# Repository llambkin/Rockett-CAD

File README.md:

# Rockett CAD

Team Rockett!

Prepare for trouble!
And make it double!

To protect the world from devastation!
To unite all peoples within our nation!

To denounce the evils of truth and love!
To extend our reach to the stars above!

Liam
Mark

Team Rocket blasts off at the speed of light!
Surrender now, or prepare to fight!

Self-hosted, browser-based **parametric CAD** for designing 3D-printable parts.
This edition is single-user and opens without accounts or sign-in.
A deliberately simplified, self-hostable take on the parametric solid-modelling
portion of Fusion 360:

> **Sketch → constrain → feature → body → timeline → modify → regenerate → export**

Built on a real B-Rep solid-modelling kernel (OpenCascade / OCCT compiled to
WebAssembly), not a mesh editor. Every operation is an editable parametric
feature in a chronological timeline; editing an earlier feature rebuilds
everything downstream against persistent topology references.

## Features

### Sketch

- **Sketcher**: draw lines, rectangles, circles, arcs, polygons, slots, points and construction geometry.
- **Constraints and dimensions**: constrain shapes with editable dimensions; relation suggestions exclude duplicates and conflicting horizontal or vertical constraints.
- **Line angles**: a typed angle is kept; double-click a line to edit its length and angle.
- **Regions**: crossing and touching curves split a sketch into regions, such as the four corners around an inscribed circle.
- **Angle snap**: hold Shift to snap a line to 15 degree steps; press A to lock its angle.
- **Offsets**: offset a curve or chain; it follows its source as the sketch changes, and its distance stays editable.
- **Project, trim and extend**: link earlier model edges into a sketch, trim the highlighted piece of a curve (T), extend curves to boundaries.
- **Insert DXF and SVG**: place DXF or SVG drawings in a sketch, or SVG on a selected face, then size, rotate and position them.
- **Edit in place**: editing a sketch rolls the model back to it; Finish Sketch returns to the saved position.

### Model

- **Solid features**: extrude, revolve, sweep, loft, emboss and deboss from sketch profiles or planar faces.
- **Modify**: fillet, chamfer, shell, combine, split, press/pull and move bodies; shell with no open face hollows the body.
- **Tangent chains**: fillet and chamfer pick smooth connected edges in one click.
- **Replicate**: mirror, rectangular pattern and circular pattern.
- **Construction**: offset planes and midplanes; sketch on any planar face.
- **Reference images**: place PNG, JPEG or WebP images on planes and calibrate them to real size.
- **Feature timeline**: rename, edit, quick edit, hover preview, suppress, delete, roll back and insert features; broken references are flagged, never dropped.

### Inspect

- **Measure**: distance, ΔXYZ, angle, radius, area and length between points, edges and faces.

### Files

- **Import**: start or extend a project from a STEP, IGES, BREP, STL, OBJ or 3MF file. Meshes are not parametric.
- **Export**: download binary STL or multi-body 3MF with named bodies and a quality setting, or exact named solids as STEP.
- **Autosave**: every change saves to a readable JSON file that keeps the full feature history.
- **Edit conflicts**: reapply or discard conflicting edits; recovery clears stale undo history so it cannot overwrite another tab’s changes.

### Workspace

- **Viewport**: orbit, pan, zoom, named views and ViewCube; visible orthographic faces remain pickable, and graphics recovery redraws automatically.
- **Toolbar**: every tool shows an icon above its label; constraints show icons only; tooltips give the shortcut key.
- **Shortcuts**: single keys start tools; ? lists every keyboard and mouse control in a resizable panel that fills the window.
- **Undo and redo**: undo any edit, even inside a sketch, separately from the feature timeline.
- **Tool panels**: list stable pick labels; closing clears their highlight, and accepting an unchanged edit creates no undo step.
- **Groups**: gather selected bodies or sketches into named, collapsible tree folders with Ctrl+G or right-click.
- **Tree selection**: Ctrl or Cmd+click adds bodies or sketches, Shift+click selects a range; right-click acts on all.
- **Live preview**: feature dialogs keep the model before the feature pickable and ghost the result, green added, red removed, until OK.
- **Right-click menus**: project rows, tree items, timeline chips and the viewport offer their actions, sketch selections their relations; right-drag still orbits.
- **Projects**: sort into folders; create, rename, move or delete by button, right-click or drag; unreadable ones show why.
- **Project files**: download a project as one `.rockett` file, or open one as a new project.
- **This browser**: keep a project in this browser instead of on the server; move it either way by Move to or drag.
- **Reload**: refreshing the page reopens the project you had open; Back returns to the list.
- **Errors**: stay visible until dismissed, and their text can be copied.
- **Version label**: the bottom-right corner shows the running build; hover for commit, version and schema.

[docs/user/guide.md](docs/user/guide.md) explains how to use each one.

## Quick start (Docker)

```bash
ROCKETT_ALLOWED_ORIGINS=http://localhost:8788 docker compose up -d
```

Then open http://localhost:8788. The server refuses to start without
`ROCKETT_ALLOWED_ORIGINS`, the comma-separated browser origins allowed to
change projects; list the origin you browse to. All state lives in the
`rockett-cad_data` volume; DOCKER.md covers LAN access, running dev and prod
side by side, and promoting the image dev verified to prod.
The container runs as the unprivileged `rockett` user: `/app` is root-owned
and `/data` is the only path it writes.

For Unraid, see [DOCKER.md](DOCKER.md) and the template in
`docker/unraid-rockett-cad.xml`.

## Running build

The bottom-right corner of the project list and the workspace shows the
running build: the image's `git describe` output, else `v<version> <commit>`,
else `v<version> dev`. Hover it for the full commit, version and schema.
`GET /api/health` returns the same fields.

A plain `docker compose up` records neither, so the label reads
`v<version> dev`. For a granular label, build with
`--build-arg ROCKETT_COMMIT=$(git rev-parse HEAD) --build-arg ROCKETT_DESCRIBE=$(git describe --tags --always --dirty)`.
[DOCKER.md](DOCKER.md) has the full Compose and `docker build` commands.

## Development

```bash
npm ci                 # .npmrc: install scripts off, exact pins on save
npm run prepare        # once per clone: husky sets core.hooksPath to .husky/_
export ROCKETT_ALLOWED_ORIGINS=http://localhost:5173
npm run dev            # server on :8788 + Vite client on :5173
npm test               # typecheck, then shared, server and client tests
npm run lint           # oxlint
npm run format:check   # Prettier
npm run lint:readme    # README feature items stay within 20 words
npm run lint:comments  # comment ratchet: no file may gain a comment
npm run lint:writing   # writing lint over tracked markdown
```

The last two need masterrulez cloned to `~/masterrulez`. See
[DEVELOPMENT.md](DEVELOPMENT.md).

## Documentation

| Doc                                        | Contents                                                          |
| ------------------------------------------ | ----------------------------------------------------------------- |
| [docs/user/guide.md](docs/user/guide.md)   | How to use each feature, controls and shortcuts                   |
| [ARCHITECTURE.md](ARCHITECTURE.md)         | System overview, layers, technology choices                       |
| [CAD_MODEL.md](CAD_MODEL.md)               | B-Rep representation, topology naming, regeneration, tessellation |
| [FEATURE_TIMELINE.md](FEATURE_TIMELINE.md) | Timeline semantics, rollback, dependency handling                 |
| [API.md](API.md)                           | REST API reference                                                |
| [DOCKER.md](DOCKER.md)                     | Deployment (Docker / Compose / Unraid)                            |
| [DEVELOPMENT.md](DEVELOPMENT.md)           | Repo layout, workflows, testing                                   |
| [WORK-ORDER.md](WORK-ORDER.md)             | Scope, rulings and planned work                                   |
| [CHANGELOG.md](CHANGELOG.md)               | Changes per release, release and schema conventions               |
| [Brief.md](Brief.md)                       | Original 3D-printing brief, kept as history                       |

## License note

Rockett CAD bundles [opencascade.js](https://github.com/donalffons/opencascade.js)
(LGPL-2.1-only), the WASM build of Open CASCADE Technology.
[THIRD-PARTY-NOTICES.md](THIRD-PARTY-NOTICES.md) lists every third-party
package in the image and the client bundle, with its version, licence and the
obligations to meet before distribution.

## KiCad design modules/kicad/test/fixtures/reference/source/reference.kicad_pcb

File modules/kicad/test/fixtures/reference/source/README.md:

# Reference source

Hand-written KiCad 9 board and inline fixture footprints. No KiCad library
footprints or models are copied. Licence: UNLICENSED, pending the project's
licence decision. This preparation adds no redistribution grant.

The two STEP models came from Rockett's named STEP exporter. Each is a
scalene triangular prism, in mm. Only trailing line whitespace was removed
from the STEP exports:

| Model           | XY vertices         | Height | Volume |
| --------------- | ------------------- | ------ | ------ |
| fixture-wedge-a | (0,0), (8,0), (1,3) | 2      | 24 mm³ |
| fixture-wedge-b | (0,0), (5,0), (0,2) | 4      | 20 mm³ |

Grammar, layers and model fields follow the
[KiCad 9 writer](https://github.com/KiCad/kicad-source-mirror/blob/286b0611feca00727bf70bfa184ec2c28a745dc3/pcbnew/pcb_io/kicad_sexpr/pcb_io_kicad_sexpr.cpp)
and [layer IDs](https://github.com/KiCad/kicad-source-mirror/blob/286b0611feca00727bf70bfa184ec2c28a745dc3/include/layer_ids.h).
The oracle script pins the official image digests from Docker Hub's
[9.0.9 metadata](https://hub.docker.com/v2/repositories/kicad/kicad/tags/9.0.9)
and [10.0.6 metadata](https://hub.docker.com/v2/repositories/kicad/kicad/tags/10.0.6).
The [KiCad 10 upgrade command](https://github.com/KiCad/kicad-source-mirror/blob/caf7377e9cb6fa1535ec3596dcb8c99bf44a996e/kicad/cli/command_pcb_upgrade.cpp)
rewrites only the copied board.

No KiCad oracle has qualified these inputs. After operator approval, preload
the pinned images separately, then run `sh scripts/make-kicad-fixtures.sh`
from the repository root with an optional new output directory. It refuses
existing outputs, never pulls images, uses absolute export origin `(0,0)`
and includes DNP models. KiCad 10 copies these inputs before upgrading.
The script's `--dry-run` prints both commands without writing files or
running Docker. Independent board and STEP checks belong to qualification.

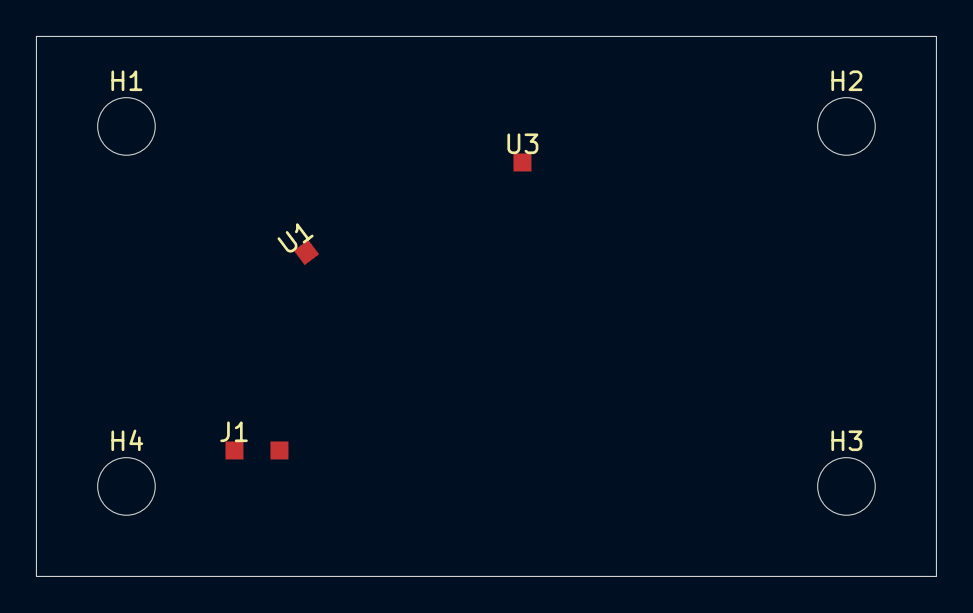
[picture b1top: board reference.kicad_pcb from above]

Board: 2 copper layers, 50.0 x 30.0 mm, 8 parts (1 on the bottom side), 2 nets, no tracks yet.

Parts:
H1, H2, H3, H4: Mount; fixture-mount
J1: Connector; fixture-connector
U1: Wedge A; fixture-rotated
U2: Wedge B; fixture-back
U3: Wedge A DNP; fixture-dnp

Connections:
GND: J1.1, U1.1, U3.1
SIGNAL: J1.2, U2.1
